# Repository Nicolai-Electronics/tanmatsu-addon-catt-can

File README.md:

# Tanmatsu add-on: CATT RS-485 & CAN adapte

This repository contains the hardware design files for the CATT RS-485 & CAN adapter.

## Documentation

Need the schematic? [It's in this repository as a PDF file](schematic.pdf).

## License

This hardware design may be used under the terms of the [CERN-OHL-P](LICENSE) license.

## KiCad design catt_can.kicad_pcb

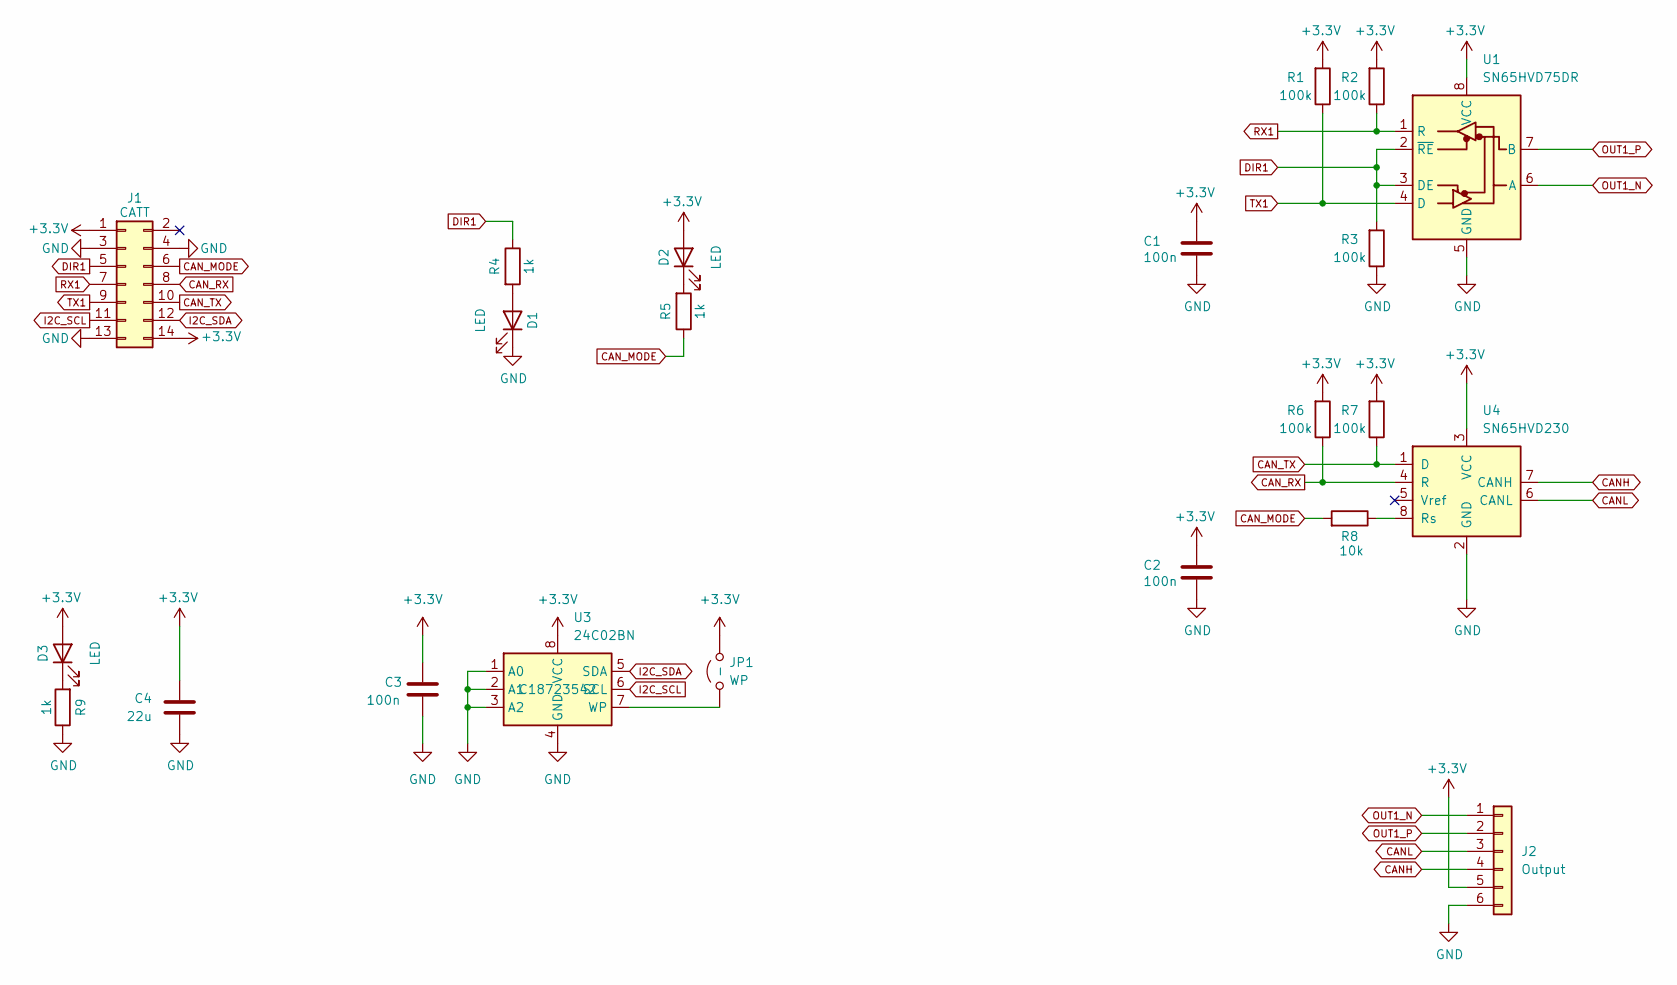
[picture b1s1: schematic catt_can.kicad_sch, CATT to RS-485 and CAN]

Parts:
C1, C2, C3: 100n; C_0402_1005Metric; LCSC C307331
C4: 22u; C_0805_2012Metric; LCSC C602037
D1, D2, D3: LED; LED_0603_1608Metric; LCSC C7496820
J1: CATT; PinHeader_2x07_P2.54mm_Horizontal; LCSC C492435
J2: Output; CONN-TH_WJ15EDGRC-3.81-6P; LCSC C7246
JP1: WP; SolderJumper-2_P1.3mm_Open_TrianglePad1.0x1.5mm
R1, R2, R3, R6, R7: 100k; R_0402_1005Metric; LCSC C25741
R4, R5, R9: 1k; R_0402_1005Metric; LCSC C11702
R8: 10k; R_0402_1005Metric
U1: SN65HVD75DR; SOIC-8_3.9x4.9mm_P1.27mm; LCSC C57928
U3: 24C02BN; SOP-8_3.9x4.9mm_P1.27mm; LCSC C18723542
U4: SN65HVD230; SOIC-8_3.9x4.9mm_P1.27mm; LCSC C12084

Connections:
+3.3V: C1.1, C2.1, C3.1, C4.1, D2.2 (A), D3.2 (A), J1.1, J1.14, J2.5, JP1.2 (B), R1.2, R2.2, R6.2, R7.2, U1.8 (VCC), U3.8 (VCC), U4.3 (VCC)
CANH: J2.4, U4.7 (CANH)
CANL: J2.3, U4.6 (CANL)
CAN_MODE: J1.6, R5.1, R8.2
CAN_RX: J1.8, R6.1, U4.4 (R)
CAN_TX: J1.10, R7.1, U4.1 (D)
DIR1: J1.5, R3.2, R4.1, U1.2 (~RE), U1.3 (DE)
GND: C1.2, C2.2, C3.2, C4.2, D1.1 (K), J1.3, J1.4, J1.13, J2.6, R3.1, R9.1, U1.5 (GND), U3.1 (A0), U3.2 (A1), U3.3 (A2), U3.4 (GND), U4.2 (GND)
I2C_SCL: J1.11, U3.6 (SCL)
I2C_SDA: J1.12, U3.5 (SDA)
unnamed: D1.2 (A), R4.2
unnamed: D2.1 (K), R5.2
unnamed: D3.1 (K), R9.2
unnamed: JP1.1 (A), U3.7 (WP)
unnamed: R8.1, U4.8 (Rs)
OUT1_N: J2.1, U1.6 (A)
OUT1_P: J2.2, U1.7 (B)
RX1: J1.7, R2.1, U1.1 (R)
TX1: J1.9, R1.1, U1.4 (D)

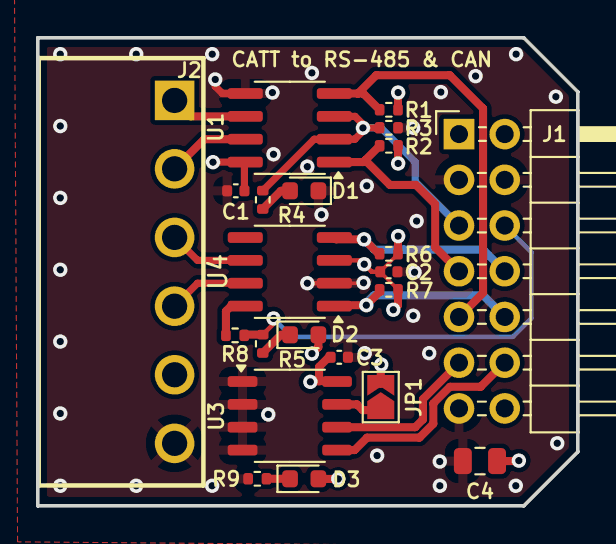
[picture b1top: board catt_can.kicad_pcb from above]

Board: 4 copper layers, 30.0 x 26.0 mm, 22 parts (0 on the bottom side), 19 nets.

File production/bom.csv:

Designator,Footprint,Quantity,Value,LCSC Part #
"C1, C2, C3",0402,3,100n,C307331
C4,0805,1,22u,C602037
"D1, D2, D3",0603,3,LED,C7496820
J1,PinHeader_2x07_P2.54mm_Horizontal,1,CATT,C492435
J2,CONN-TH_WJ15EDGRC-3.81-6P,1,Output,C7246
"R1, R2, R3, R6, R7",0402,5,100k,C25741
"R4, R5, R9",0402,3,1k,C11702
R8,0402,1,10k,
U1,SOIC-8_3.9x4.9mm_P1.27mm,1,SN65HVD75DR,C57928
U3,SOP-8_3.9x4.9mm_P1.27mm,1,24C02BN,C18723542
U4,SOIC-8_3.9x4.9mm_P1.27mm,1,SN65HVD230,

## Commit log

2025-05-20 Add production files
2025-05-20 Fix typo in readme
